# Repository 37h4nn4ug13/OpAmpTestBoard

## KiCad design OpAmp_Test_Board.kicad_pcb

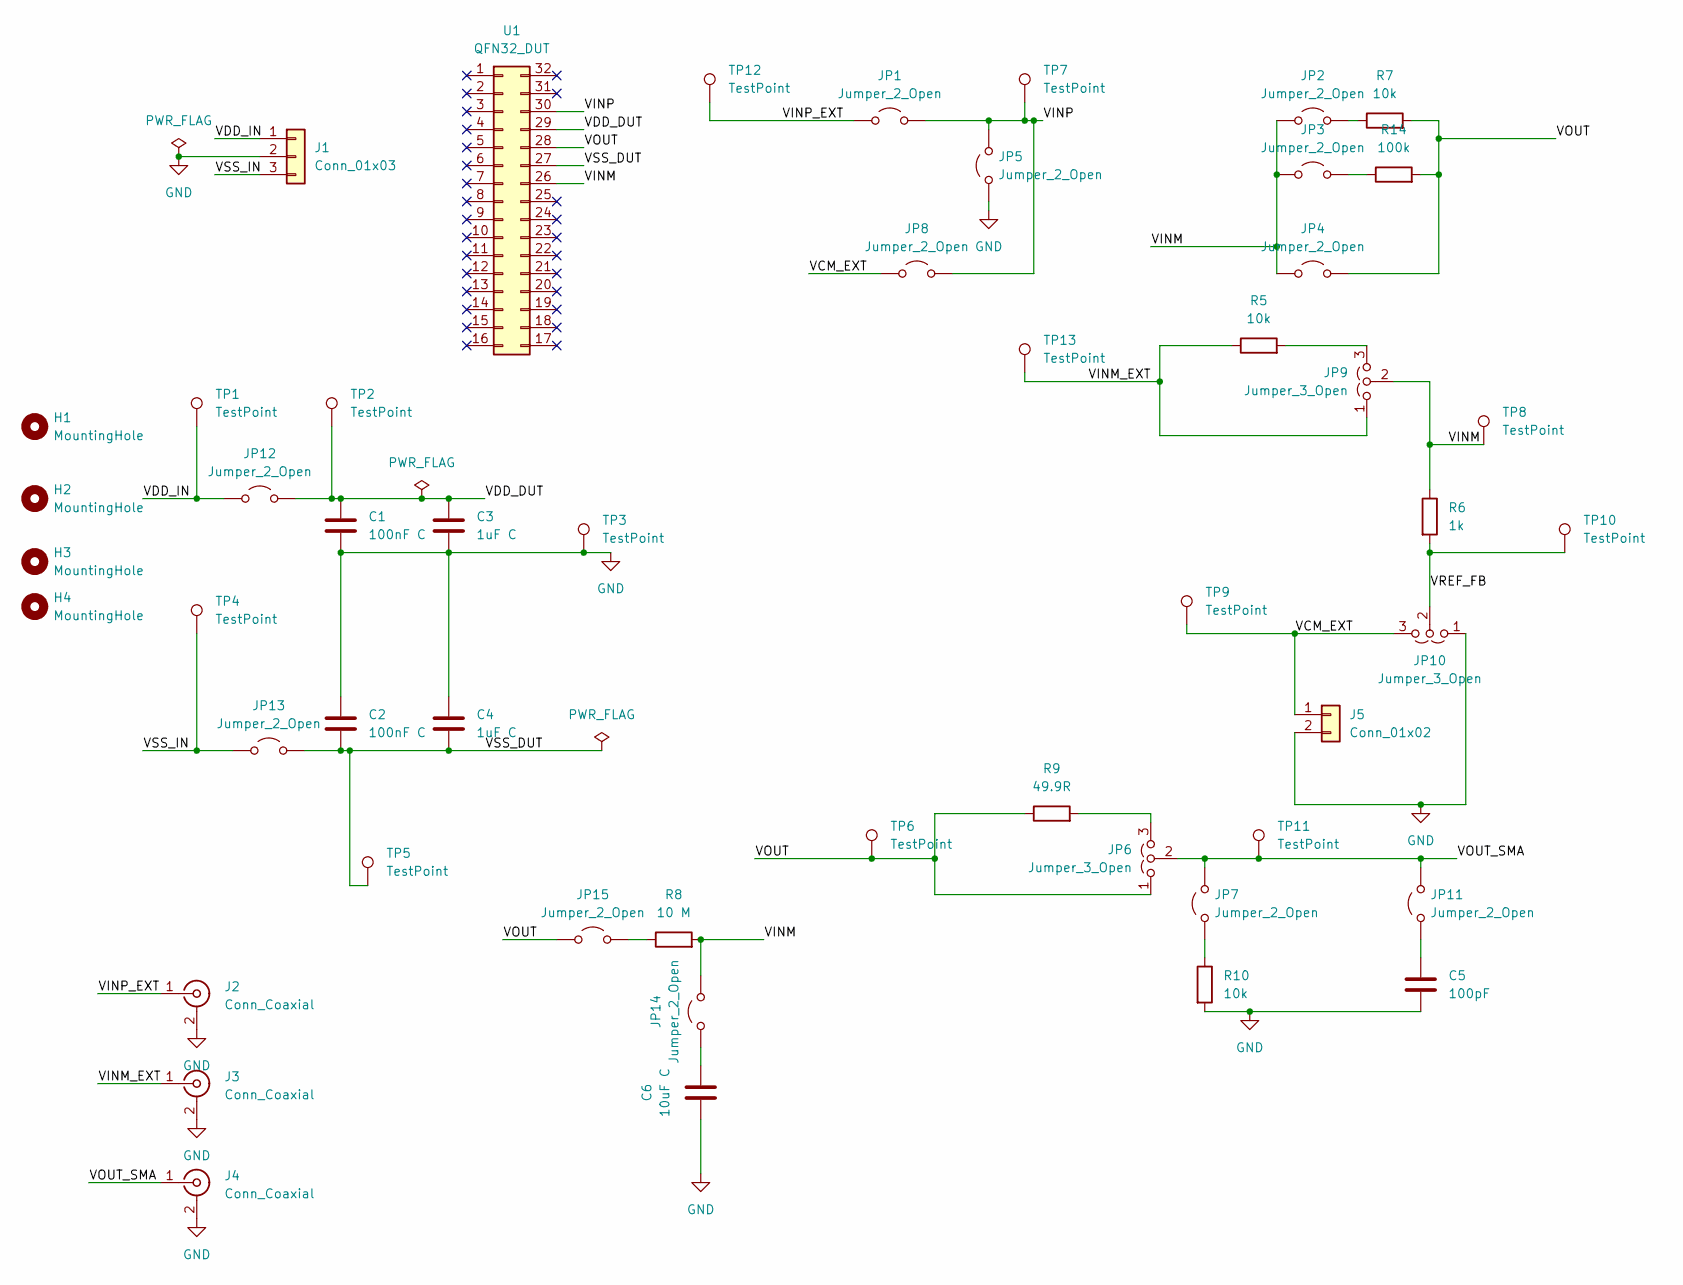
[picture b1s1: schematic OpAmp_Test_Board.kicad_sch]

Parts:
C1, C2: 100nF C; C_0603_1608Metric
C3, C4: 1uF C; C_0603_1608Metric
C5: 100pF; C_0603_1608Metric
C6: 10uF C; C_0603_1608Metric
H1, H2, H3, H4: MountingHole; MountingHole_3.2mm_M3
J1: Conn_01x03; TerminalBlock_MaiXu_MX126-5.0-03P_1x03_P5.00mm
J2, J3, J4: Conn_Coaxial; SMA_Molex_73251-2120_EdgeMount_Horizontal
J5: Conn_01x02; TerminalBlock_MaiXu_MX126-5.0-02P_1x02_P5.00mm
JP1, JP2, JP3, JP4, JP5, JP7, JP8, JP11, JP12, JP13, JP14, JP15: Jumper_2_Open; PinHeader_1x02_P2.54mm_Vertical
JP6, JP9, JP10: Jumper_3_Open; PinHeader_1x03_P2.54mm_Vertical
R5, R7, R10: 10k; R_0603_1608Metric
R6: 1k; R_0603_1608Metric
R8: 10 M; R_0603_1608Metric
R9: 49.9R; R_0603_1608Metric
R14: 100k; R_0603_1608Metric
TP1, TP2, TP3, TP4, TP5: TestPoint; TestPoint_Loop_D2.50mm_Drill1.0mm
TP6, TP9, TP10, TP11, TP12, TP13: TestPoint; TestPoint_Pad_D1.5mm
TP7, TP8: TestPoint; TestPoint_Pad_D1.0mm
U1: QFN32_DUT; Plastronics_32LQ65S17070

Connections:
/VCM_EXT: J5.1, JP8.1 (A), JP10.3 (B), TP9.1 (1_1)
/VDD_DUT: C1.1, C3.1, JP12.2 (B), TP2.1 (1_1), U1.29 (VDD)
/VDD_IN: J1.1, JP12.1 (A), TP1.1 (1_1)
/VINM: JP2.1 (A), JP3.1 (A), JP4.1 (A), JP9.2 (C), JP14.2 (B), R6.1, R8.2, TP8.1 (1_1), U1.26 (VINM)
/VINM_EXT: J3.1 (In), JP9.1 (A), R5.1, TP13.1 (1_1)
/VINP: JP1.2 (B), JP5.2 (B), JP8.2 (B), TP7.1 (1_1), U1.30 (VINP)
/VINP_EXT: J2.1 (In), JP1.1 (A), TP12.1 (1_1)
/VOUT: JP4.2 (B), JP6.1 (A), JP15.1 (A), R7.2, R9.1, R14.2, TP6.1 (1_1), U1.28 (VOUT)
/VOUT_SMA: J4.1 (In), JP6.2 (C), JP7.2 (B), JP11.2 (B), TP11.1 (1_1)
/VREF_FB: JP10.2 (C), R6.2, TP10.1 (1_1)
/VSS_DUT: C2.2, C4.2, JP13.2 (B), TP5.1 (1_1), U1.27 (VSS)
/VSS_IN: J1.3, JP13.1 (A), TP4.1 (1_1)
GND: C1.2, C2.1, C3.2, C4.1, C5.2, C6.1, J1.2, J2.2 (Ext), J3.2 (Ext), J4.2 (Ext), J5.2, JP5.1 (A), JP10.1 (A), R10.2, TP3.1 (1_1)
unnamed: JP2.2 (B), R7.1
unnamed: JP3.2 (B), R14.1
unnamed: JP6.3 (B), R9.2
unnamed: JP7.1 (A), R10.1
unnamed: JP9.3 (B), R5.2
unnamed: C5.1, JP11.1 (A)
unnamed: C6.2, JP14.1 (A)
unnamed: JP15.2 (B), R8.1

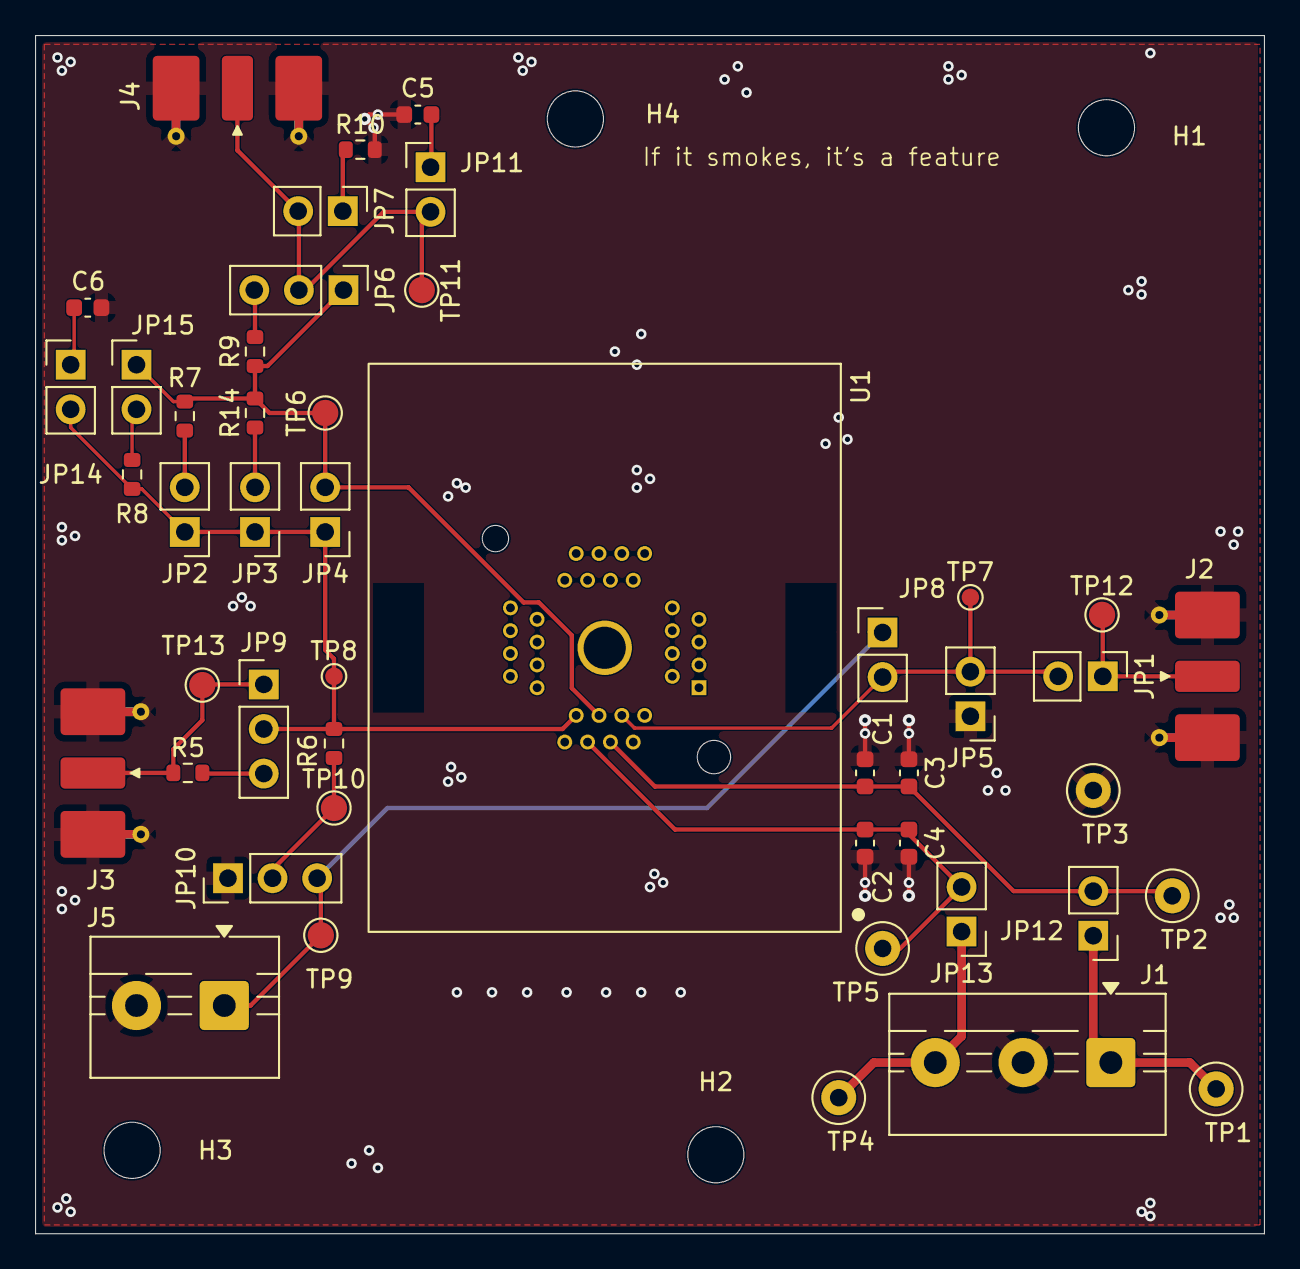
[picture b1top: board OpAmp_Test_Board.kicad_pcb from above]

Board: 2 copper layers, 70.0 x 68.2 mm, 51 parts (0 on the bottom side), 21 nets.
